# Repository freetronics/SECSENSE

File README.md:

Security Sensor Shield for Arduino
==================================
Copyright 2013 Freetronics Pty Ltd  
Freetronics site:  www.freetronics.com  
Freetronics email: info@freetronics.com  

Based on the circuit described in the "Security / Automation Sensors"
project in the book "Practical Arduino", this shield allows up to 4
security sensors to be connected with full End-Of-Line (EOL) support to
detect tampering.

Supported sensors include:

 * PIR (passive infrared) motion detectors.
 * Microwave motion detectors.
 * Reed switches.
 * Glass break detectors.
 * Gas detectors.

End-Of-Line technology allows the system to detect a variety of events
using a single cable pair to the sensor, including:

 * Sensor triggered.
 * Sensor cable cut.
 * Sensor cable short-circuited.
 * Sensor housing opened (even when system is disarmed)

Compatible with the Freetronics Eleven, Arduino Uno, and other
compatible boards based on the same header format.

Features:

 * Supports 4 sensor channels simultaneously.
 * Sensor power supply connections totally isolated from the Arduino.
 * Status LED for each sensor channel.
 * Reset button wired through to Arduino reset pin.
 * Green "Sensor power on" LED.
 * Blue "Arduino power on" LED.
 * Overlay guide where you need it: both top and bottom.

More information is available at:

  http://www.freetronics.com/secsense  
  http://www.practicalarduino.com/projects/security-sensors

INSTALLATION
------------
The design is saved as an EAGLE project. EAGLE PCB design software is
available from www.cadsoftusa.com free for non-commercial use. To use
this project download it and place the directory containing these files
into the "eagle" directory on your computer. Then open EAGLE and
navigate to Projects -> eagle -> SECSENSE.

DISTRIBUTION
------------
The specific terms of distribution of this project are governed by the
license referenced below.

LICENSE
-------
Licensed under the TAPR Open Hardware License (www.tapr.org/OHL).
The "license" folder within this repository also contains a copy of
this license in plain text format.

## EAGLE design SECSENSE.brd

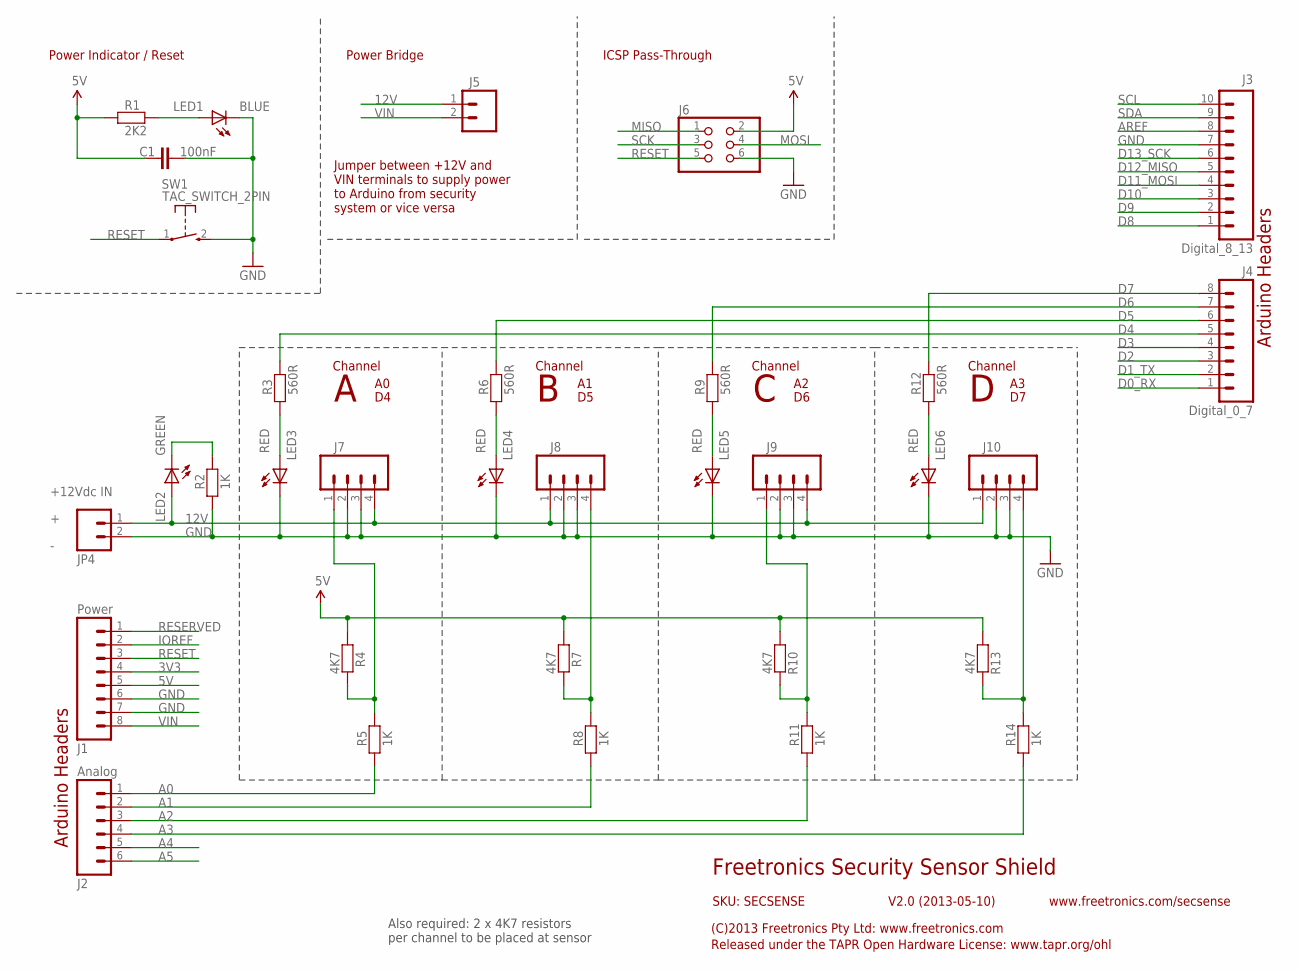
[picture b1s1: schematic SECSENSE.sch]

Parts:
C1: 100nF; 0603
J1: Power; 1X08
J2: Analog; 1X06
J3: Digital_8_13; 1X10
J4: Digital_0_7; 1X08
J5: M02PTH; 1X02
J6: PINHD-2X3; 2X03
J7, J8, J9, J10: M04SCREW; SCREWTERMINAL-3.5MM-4
JP4: M023.5MM; SCREWTERMINAL-3.5MM-2
LED1: BLUE; LED-0603
LED2: GREEN; LED-0603
LED3, LED4, LED5, LED6: RED; LED-0603
R1: 2K2; 0603
R2, R5, R8, R11, R14: 1K; 0603
R3, R6, R9, R12: 560R; 0603
R4, R7, R10, R13: 4K7; 0603
SW1: TAC_SWITCH_2PIN; TACTILE_SWITCH_SMD_2PIN_TINY

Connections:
3V3: J1.4
5V: C1.1, J1.5, J6.2, R1.1, R4.1, R7.1, R10.1, R13.1
12V: J5.1, J7.4, J8.1, J9.4, J10.1, JP4.1, LED2.A
A0: J2.1, R5.1
A1: J2.2, R8.1
A2: J2.3, R11.1
A3: J2.4, R14.1
A4: J2.5
A5: J2.6
AREF: J3.8
D0_RX: J4.1
D1_TX: J4.2
D2: J4.3
D3: J4.4
D4: J4.5, R3.2
D5: J4.6, R6.2
D6: J4.7, R9.2
D7: J4.8, R12.2
D8: J3.1
D9: J3.2
D10: J3.3
D11_MOSI: J3.4
D12_MISO: J3.5
D13_SCK: J3.6
GND: C1.2, J1.6, J1.7, J3.7, J6.6, J7.2, J7.3, J8.2, J8.3, J9.2, J9.3, J10.2, J10.3, JP4.2, LED1.C, LED3.C, LED4.C, LED5.C, LED6.C, R2.1, SW1.2 (S)
IOREF: J1.2
MISO: J6.1
MOSI: J6.4
unnamed: LED2.C, R2.2
unnamed: LED1.A, R1.2
unnamed: J8.4, R7.2, R8.2
unnamed: J9.1, R10.2, R11.2
unnamed: LED6.A, R12.1
unnamed: LED5.A, R9.1
unnamed: LED4.A, R6.1
unnamed: LED3.A, R3.1
unnamed: J10.4, R13.2, R14.2
unnamed: J7.1, R4.2, R5.2
RESERVED: J1.1
RESET: J1.3, J6.5, SW1.1
SCK: J6.3
SCL: J3.10
SDA: J3.9
VIN: J1.8, J5.2

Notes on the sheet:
Power Indicator / Reset
Arduino Headers
Channel
Power Bridge
Jumper between +12V and VIN terminals to supply power to Arduino from security system or vice versa
+12Vdc IN
Freetronics Security Sensor Shield
V2.0 (2013-05-10)
SKU: SECSENSE
(C)2013 Freetronics Pty Ltd: www.freetronics.com
Released under the TAPR Open Hardware License: www.tapr.org/ohl
www.freetronics.com/secsense
ICSP Pass-Through
Also required: 2 x 4K7 resistors per channel to be placed at sensor

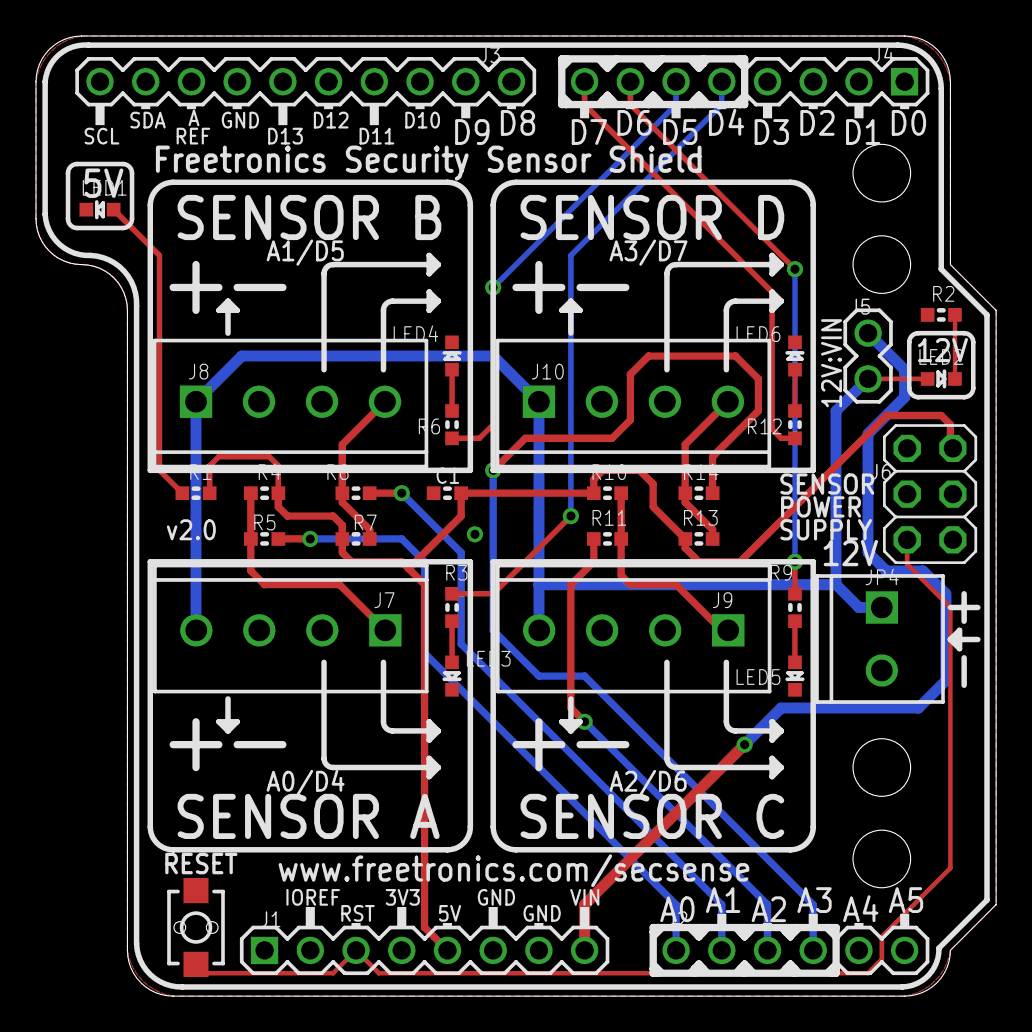
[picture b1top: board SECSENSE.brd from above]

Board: 2 copper layers, 53.3 x 53.3 mm, 33 parts (0 on the bottom side), 23 nets.

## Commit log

2015-04-08 Initial import using new layout, ready for v2.0 release
2019-04-24 Improve designators

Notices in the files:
parts and their libraries:
freetronics-original: Licensing: CC v3.0 Share-Alike You are welcome to use this library for commercial purposes.
